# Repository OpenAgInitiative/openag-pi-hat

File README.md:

# openag-pi-hat
This hat is a simple connector breakout board to simplify the wiring on the brain box. It is the first step toward a more comprehensive brain box PCB. 

## Board

## Schematic

## Fabrication Instructions
1. Gerber files are included in this repo, send them to a pcb fab house. Use OSH Park for low volume / low cost. Use Advanced Circuits for high volume / fast turn time.
2. Bill of materials can be found in the repo, order as needed
3. Solder components to the PCB

## Adafruit-Perma-Proto-HAT-PCB README
This repo was forked from the Adafruit-Perma-Proto-HAT-PCB
```
Format is EagleCAD schematic and board layout

For more details, check out the product page at

-----> https://www.adafruit.com/products/2310

-----> https://www.adafruit.com/products/2314

Adafruit invests time and resources providing this open source design, 
please support Adafruit and open-source hardware by purchasing 
products from Adafruit!

Designed by Adafruit Industries.  
Creative Commons Attribution, Share-Alike license, check license.txt for more information
All text above must be included in any redistribution
```

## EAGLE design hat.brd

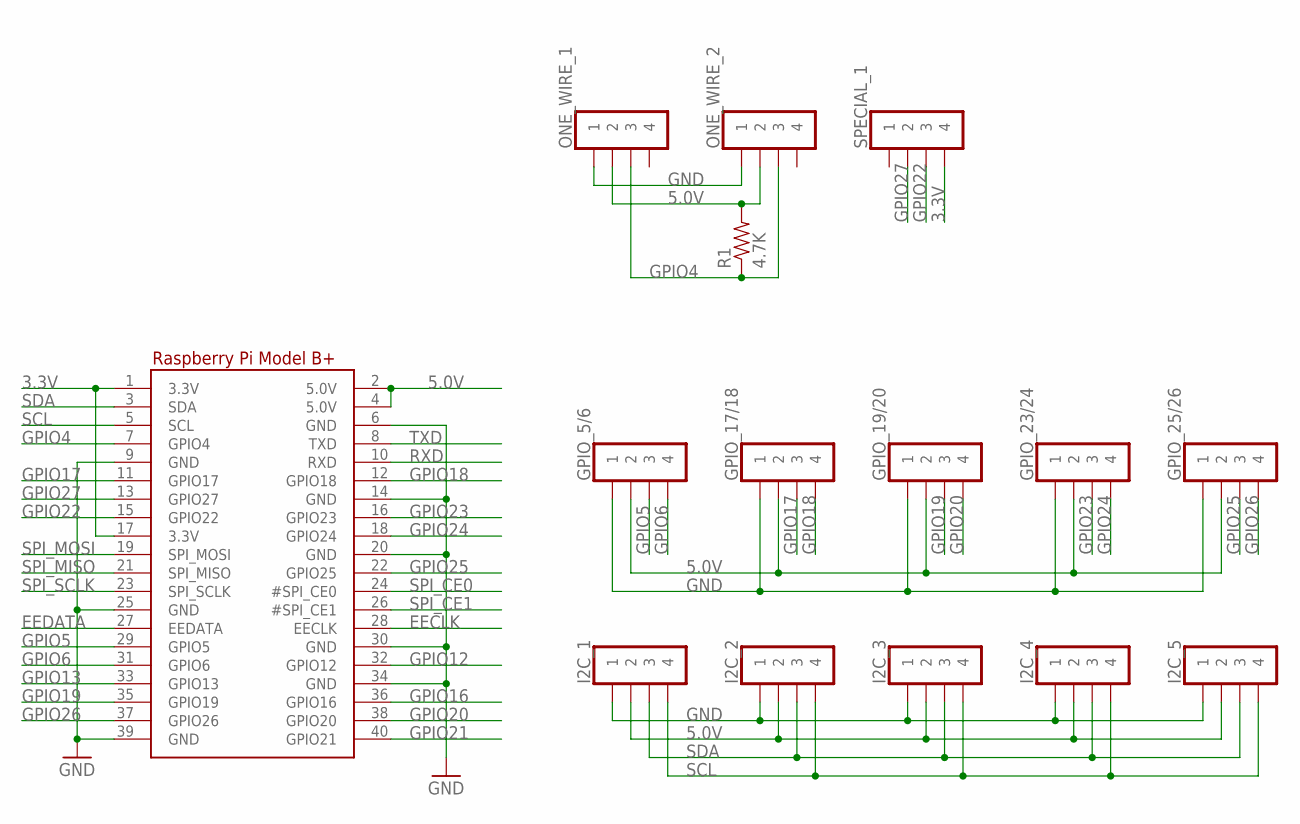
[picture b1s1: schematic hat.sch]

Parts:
GPIO_5/6, GPIO_17/18, GPIO_19/20, GPIO_23/24, GPIO_25/26: MOLEX_0705430003
I2C_1, I2C_2, I2C_3, I2C_4, I2C_5: MOLEX_0705430003
ONE_WIRE_1, ONE_WIRE_2: MOLEX_0705430003
R1: 4.7K; AXIAL-0.3
RPI1: RASPBERRYPI_BPLUS_HATNOSLOTS; PI_HAT_NOSLOTS
SPECIAL_1: MOLEX_0705430003

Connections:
3.3V: RPI1.1 (3.3V), RPI1.17 (3.3V), SPECIAL_1.4
5.0V: GPIO_5/6.2, GPIO_17/18.2, GPIO_19/20.2, GPIO_23/24.2, GPIO_25/26.2, I2C_1.2, I2C_2.2, I2C_3.2, I2C_4.2, I2C_5.2, ONE_WIRE_1.2, ONE_WIRE_2.2, R1.P$2 (2), RPI1.2 (5.0V), RPI1.4 (5.0V)
EECLK: RPI1.28 (EECLK)
EEDATA: RPI1.27 (EEDATA)
GND: GPIO_5/6.1, GPIO_17/18.1, GPIO_19/20.1, GPIO_23/24.1, GPIO_25/26.1, I2C_1.1, I2C_2.1, I2C_3.1, I2C_4.1, I2C_5.1, ONE_WIRE_1.1, ONE_WIRE_2.1, RPI1.6 (GND), RPI1.9 (GND), RPI1.14 (GND), RPI1.20 (GND), RPI1.25 (GND), RPI1.30 (GND), RPI1.34 (GND), RPI1.39 (GND)
GPIO4: ONE_WIRE_1.3, ONE_WIRE_2.3, R1.P$1 (1), RPI1.7 (GPIO4)
GPIO5: GPIO_5/6.3, RPI1.29 (GPIO5)
GPIO6: GPIO_5/6.4, RPI1.31 (GPIO6)
GPIO12: RPI1.32 (GPIO12)
GPIO13: RPI1.33 (GPIO13)
GPIO16: RPI1.36 (GPIO16)
GPIO17: GPIO_17/18.3, RPI1.11 (GPIO17)
GPIO18: GPIO_17/18.4, RPI1.12 (GPIO18)
GPIO19: GPIO_19/20.3, RPI1.35 (GPIO19)
GPIO20: GPIO_19/20.4, RPI1.38 (GPIO20)
GPIO21: RPI1.40 (GPIO21)
GPIO22: RPI1.15 (GPIO22), SPECIAL_1.3
GPIO23: GPIO_23/24.3, RPI1.16 (GPIO23)
GPIO24: GPIO_23/24.4, RPI1.18 (GPIO24)
GPIO25: GPIO_25/26.3, RPI1.22 (GPIO25)
GPIO26: GPIO_25/26.4, RPI1.37 (GPIO26)
GPIO27: RPI1.13 (GPIO27), SPECIAL_1.2
RXD: RPI1.10 (RXD)
SCL: I2C_1.4, I2C_2.4, I2C_3.4, I2C_4.4, I2C_5.4, RPI1.5 (SCL)
SDA: I2C_1.3, I2C_2.3, I2C_3.3, I2C_4.3, I2C_5.3, RPI1.3 (SDA)
SPI_CE0: RPI1.24 (#SPI_CE0)
SPI_CE1: RPI1.26 (#SPI_CE1)
SPI_MISO: RPI1.21 (SPI_MISO)
SPI_MOSI: RPI1.19 (SPI_MOSI)
SPI_SCLK: RPI1.23 (SPI_SCLK)
TXD: RPI1.8 (TXD)

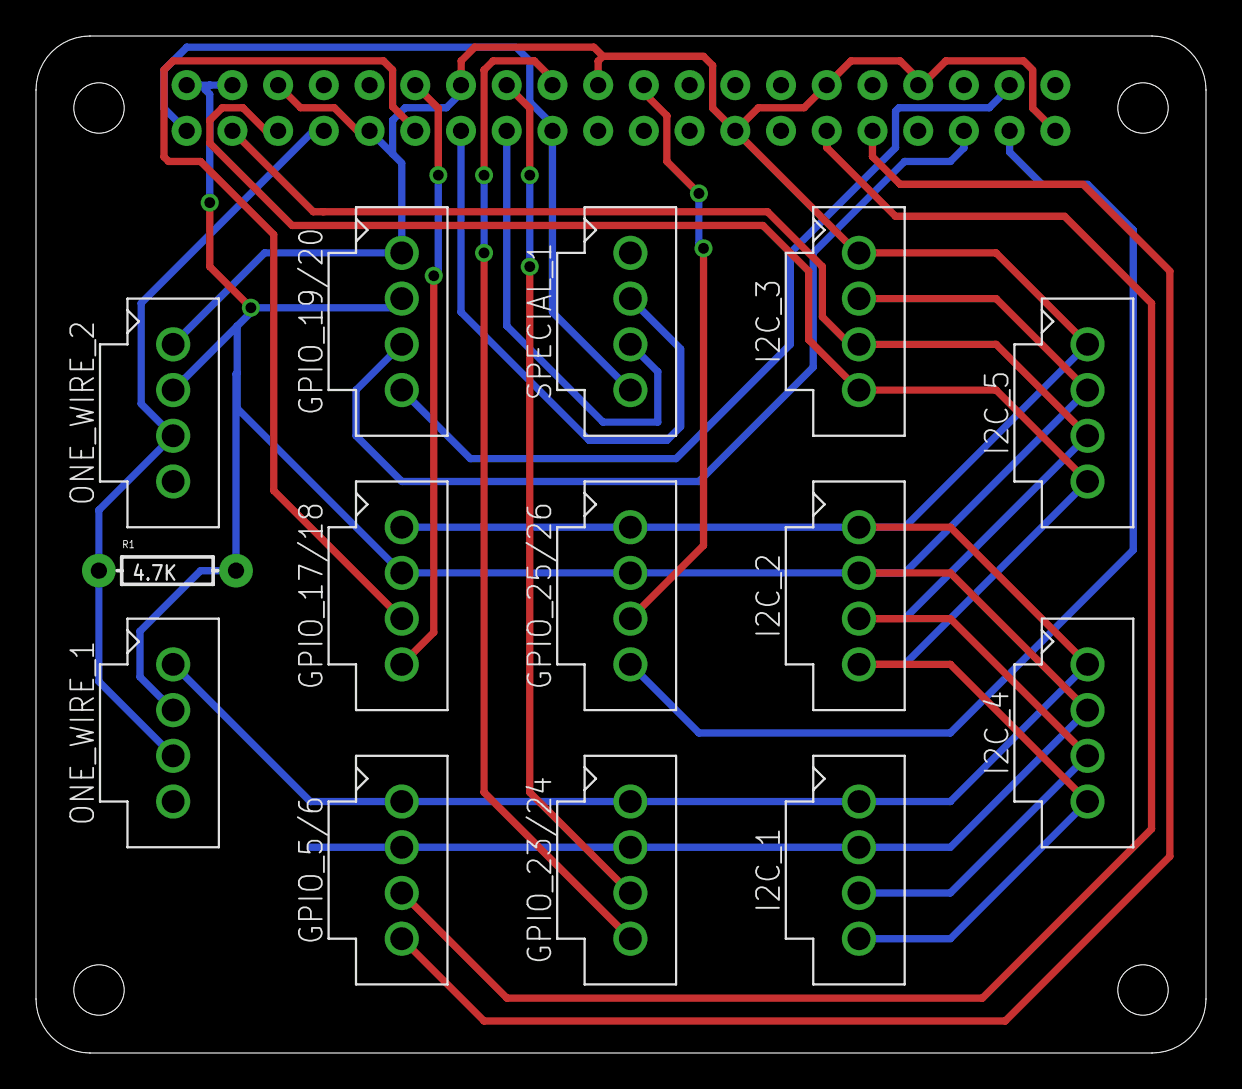
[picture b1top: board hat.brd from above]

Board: 2 copper layers, 65.0 x 56.5 mm, 15 parts (0 on the bottom side), 18 nets.

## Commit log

2017-05-23 Rename Adafruit HaD Proto HAT rev A.brd to hat_template.brd
2017-05-23 Rename Adafruit HaD Proto HAT rev A.sch to hat_template.sch
2017-05-25 simple connector breakout board
2017-05-25 initial documentation
2017-05-25 pictures from eagle!
2017-05-25 fix image links

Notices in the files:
parts and their libraries:
microbuilder: This work is placed in the public domain, and may be freely used for commercial and non-commercial work with the following conditions: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
